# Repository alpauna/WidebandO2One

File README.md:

WidebandO2One
==
First Wideband O2 Controller for Bosch LS 4.9 Sensors. I hope to add more complex controllers in the future that is why I named it "WidebandO2One"
Also, because it is going to control only one sensor. I plan on a two as well and will add that to my [Megasquirt projects](https://alshowto.com/tag/megasquirt/). 

Key Elements
--
* Uses ATTiny 1626 micorprocessor as the micro as they are cheap and easy to program. It is using the Arduino code base.
* Wideband O2 blog [here](https://alshowto.com/wideband-o2-one/) for more details. 
* Uses the Bosch CJ125 controller chip as the basis of sensor control.
* More to come as project expands into my [99 Ford F150](https://alshowto.com/category/electronics/99-f150-rebuild/) project.

So far, I only have the schematics done. Code to follow shortly, but loosely based on Arduino shield code from [here](http://www.bylund-automotive.com/educative/lambda/).

**Note: All Schematics are written in [KiCad](https://www.kicad.org/).**

Works Only With LS 4.9 sensors
--
 * However, with some rework it will work with 4.2 Sensors, but I am not sure why one would use 4.2

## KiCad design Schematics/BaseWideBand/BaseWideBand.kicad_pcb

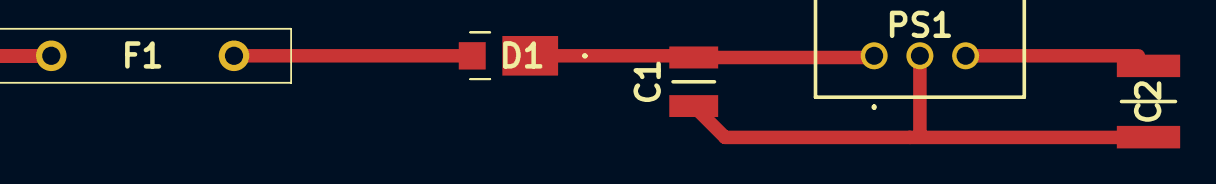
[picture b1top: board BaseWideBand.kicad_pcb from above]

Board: 2 copper layers, 5 parts (0 on the bottom side), 4 nets.

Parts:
C1: UMJ325KB7106KMHT; CAPC3225X280N
C2: C1812C206K3RLCAUTO; CAPC4532X370N
D1: V8PAN50-M3_I; V8PAN50M3I
F1: RUEF600
PS1: VR10S05

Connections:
5v 1a: C2.1, PS1.3 (+VOUT)
GND: C1.1, C2.2, PS1.2 (GROUND)
unnamed: C1.2, D1.1, PS1.1 (+VIN)
unnamed: D1.2, F1.2

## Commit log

2022-04-21 First commit of current state
    Wideband O2 One is a single sensor controller for Bosch LS 4.9 Oxygen sensor.
2022-04-21 Created first readme file
